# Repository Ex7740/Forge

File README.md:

# **FORGE**

Forge is a custom stm32 based board that will be the basis of me learning electronics schematics and pcb layout whilst at university

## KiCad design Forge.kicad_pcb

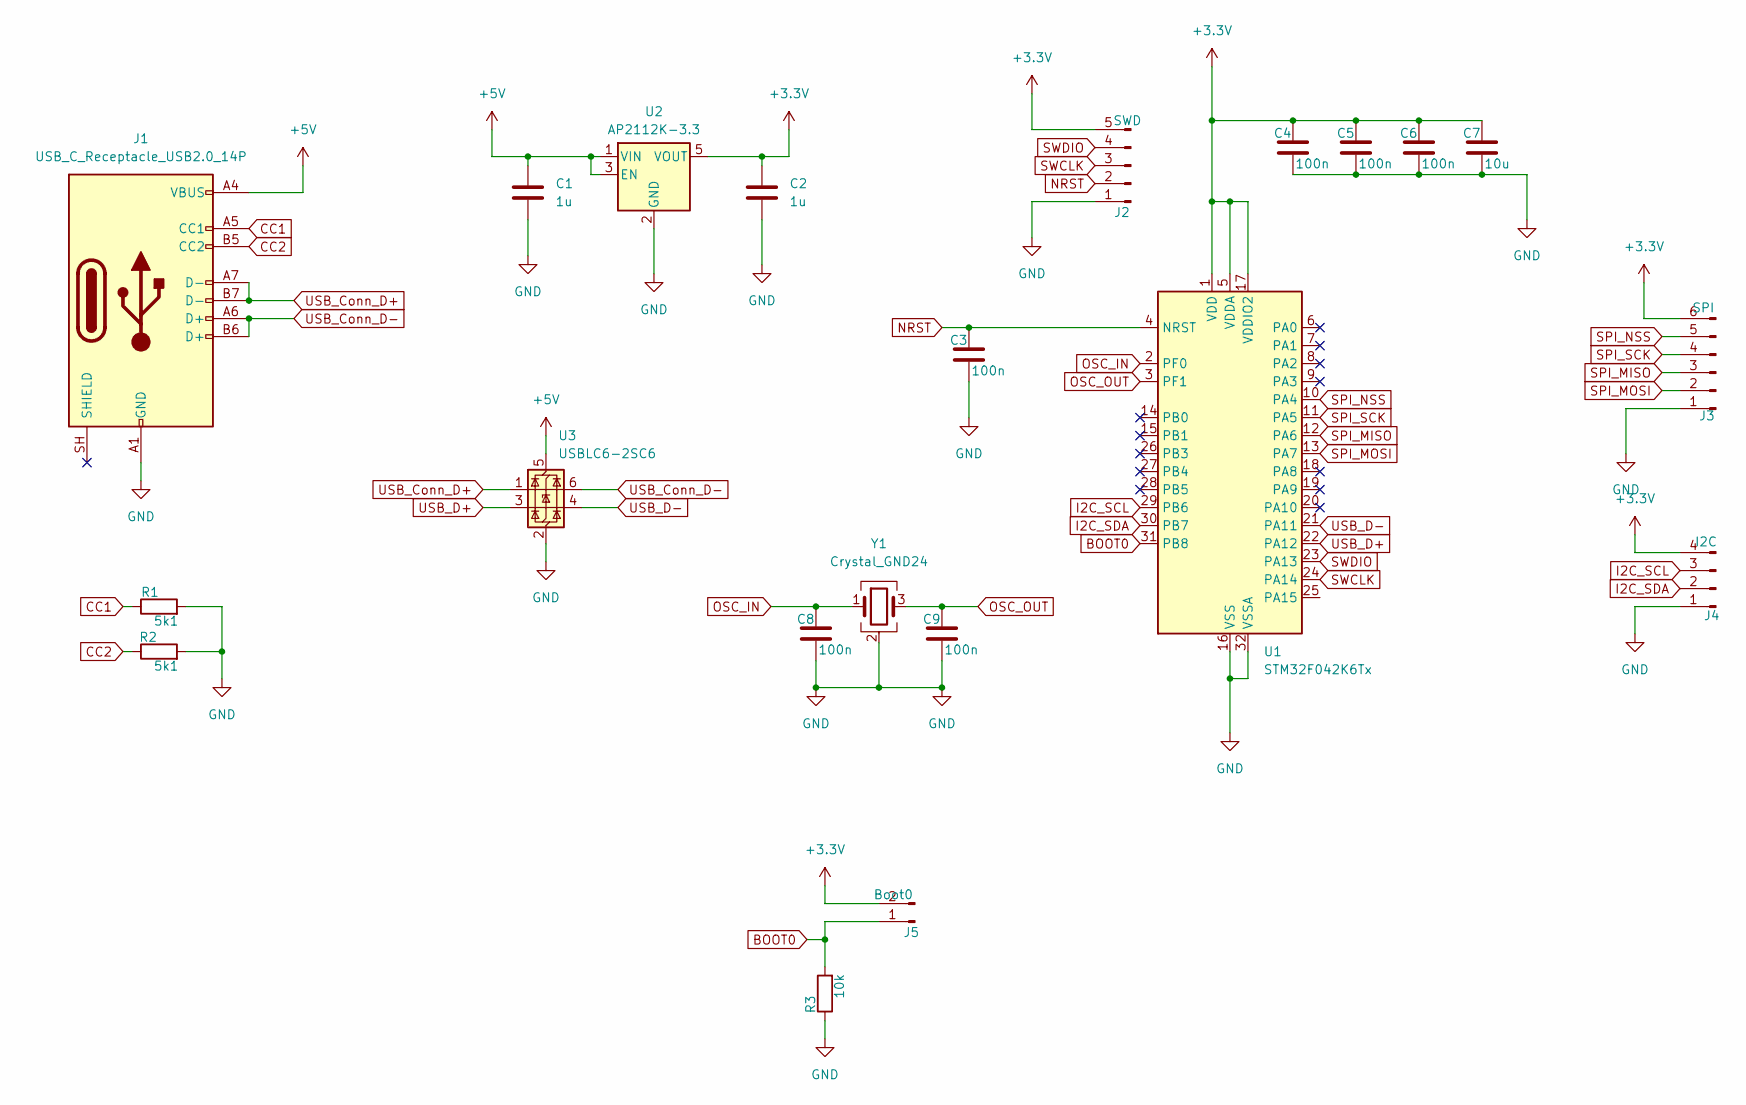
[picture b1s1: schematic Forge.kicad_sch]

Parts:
C1, C2: 1u; C_0805_2012Metric_Pad1.18x1.45mm_HandSolder
C3, C4, C5, C6: 100n; C_0805_2012Metric_Pad1.18x1.45mm_HandSolder
C7: 10u; C_0805_2012Metric_Pad1.18x1.45mm_HandSolder
C8, C9: 100n; C_0603_1608Metric_Pad1.08x0.95mm_HandSolder
J1: USB_C_Receptacle_USB2.0_14P; USB_C_Receptacle_GCT_USB4105-xx-A_16P_TopMnt_Horizontal
J2: SWD; PinHeader_1x05_P2.54mm_Vertical
J3: SPI; PinHeader_1x06_P2.54mm_Vertical
J4: I2C; PinHeader_1x04_P2.54mm_Vertical
J5: Boot0; PinHeader_1x02_P2.54mm_Vertical
R1, R2: 5k1; R_0805_2012Metric_Pad1.20x1.40mm_HandSolder
R3: 10k; R_0805_2012Metric_Pad1.20x1.40mm_HandSolder
U1: STM32F042K6Tx; LQFP-32_7x7mm_P0.8mm
U2: AP2112K-3.3; SOT-23-5
U3: USBLC6-2SC6; SOT-23-6
Y1: Crystal_GND24; Crystal_SMD_EuroQuartz_MT-4Pin_3.2x2.5mm_HandSoldering

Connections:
+3.3V: C2.1, C4.1, C5.1, C6.1, C7.1, J2.5, J3.6, J4.4, J5.2, U1.1 (VDD), U1.5 (VDDA), U1.17 (VDDIO2), U2.5 (VOUT)
+5V: C1.1, J1.A4 (VBUS), J1.A9 (VBUS), J1.B4 (VBUS), J1.B9 (VBUS), U2.1 (VIN), U2.3 (EN), U3.5 (VBUS)
BOOT0: J5.1, R3.2, U1.31 (PB8)
CC1: J1.A5 (CC1), R1.1
CC2: J1.B5 (CC2), R2.1
GND: C1.2, C2.2, C3.2, C4.2, C5.2, C6.2, C7.2, C8.2, C9.2, J1.A1 (GND), J1.A12 (GND), J1.B1 (GND), J1.B12 (GND), J2.1, J3.1, J4.1, R1.2, R2.2, R3.1, U1.16 (VSS), U1.32 (VSSA), U2.2 (GND), U3.2 (GND), Y1.2 (G), Y1.4 (G)
I2C_SCL: J4.3, U1.29 (PB6)
I2C_SDA: J4.2, U1.30 (PB7)
NRST: C3.1, J2.2, U1.4 (NRST)
OSC_IN: C8.1, U1.2 (PF0), Y1.1
OSC_OUT: C9.1, U1.3 (PF1), Y1.3
SPI_MISO: J3.3, U1.12 (PA6)
SPI_MOSI: J3.2, U1.13 (PA7)
SPI_NSS: J3.5, U1.10 (PA4)
SPI_SCK: J3.4, U1.11 (PA5)
SWCLK: J2.3, U1.24 (PA14)
SWDIO: J2.4, U1.23 (PA13)
USB_Conn_D+: J1.A7 (D-), J1.B7 (D-), U3.1 (I/O1)
USB_Conn_D-: J1.A6 (D+), J1.B6 (D+), U3.6 (I/O1)
USB_D+: U1.22 (PA12), U3.3 (I/O2)
USB_D-: U1.21 (PA11), U3.4 (I/O2)

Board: 2 copper layers, 21 parts (0 on the bottom side), 21 nets, no tracks yet.
